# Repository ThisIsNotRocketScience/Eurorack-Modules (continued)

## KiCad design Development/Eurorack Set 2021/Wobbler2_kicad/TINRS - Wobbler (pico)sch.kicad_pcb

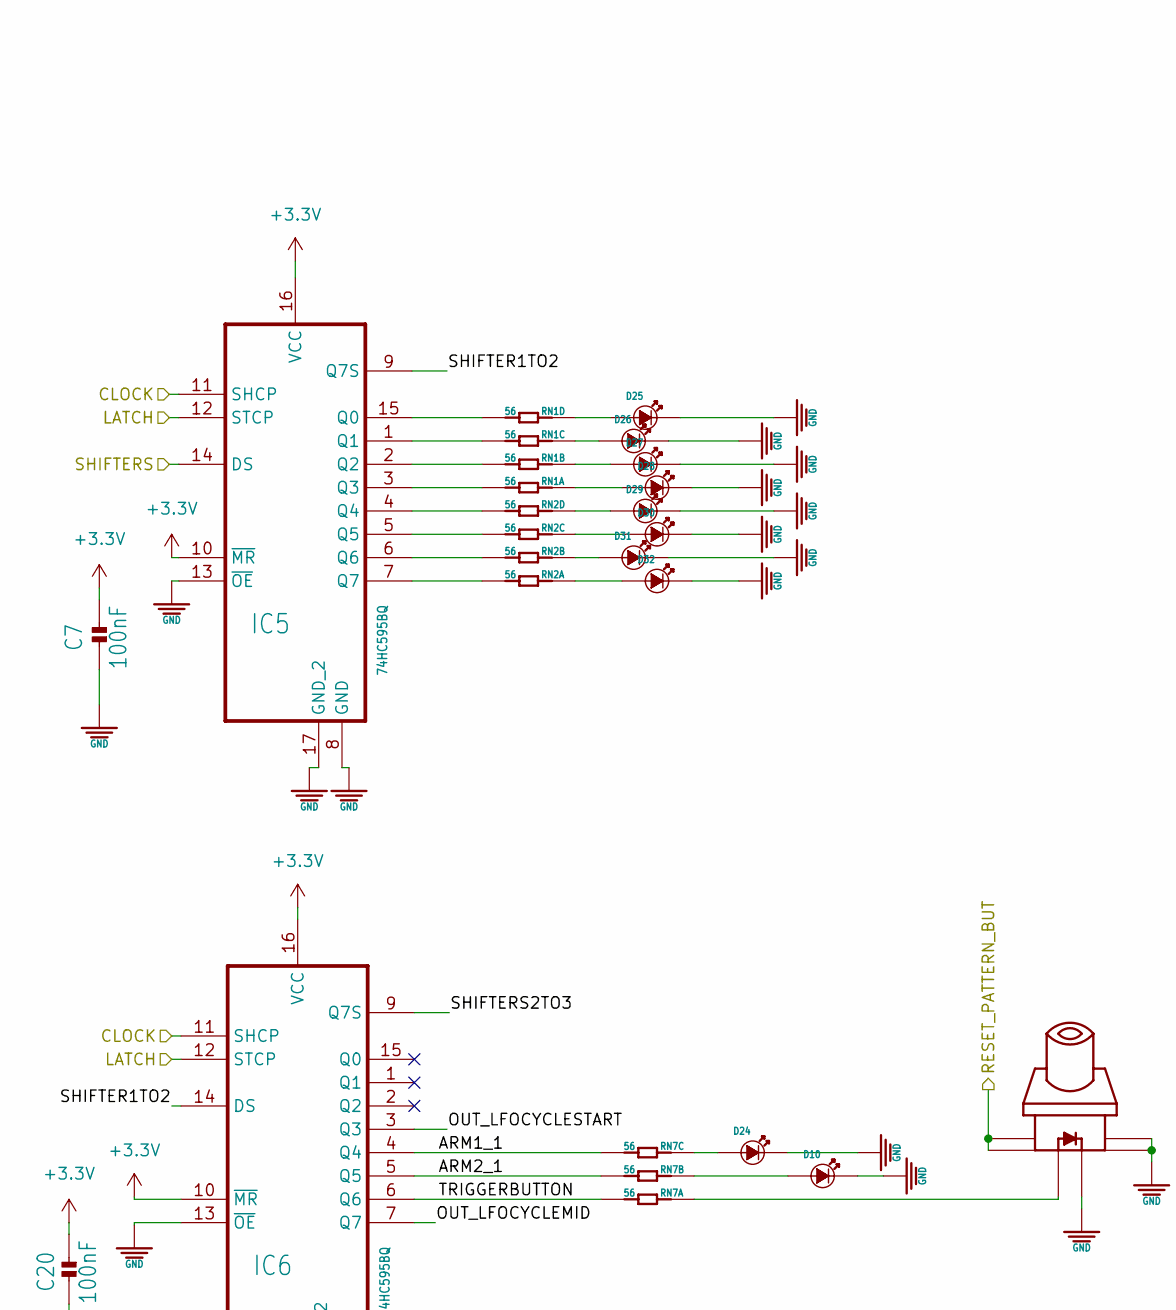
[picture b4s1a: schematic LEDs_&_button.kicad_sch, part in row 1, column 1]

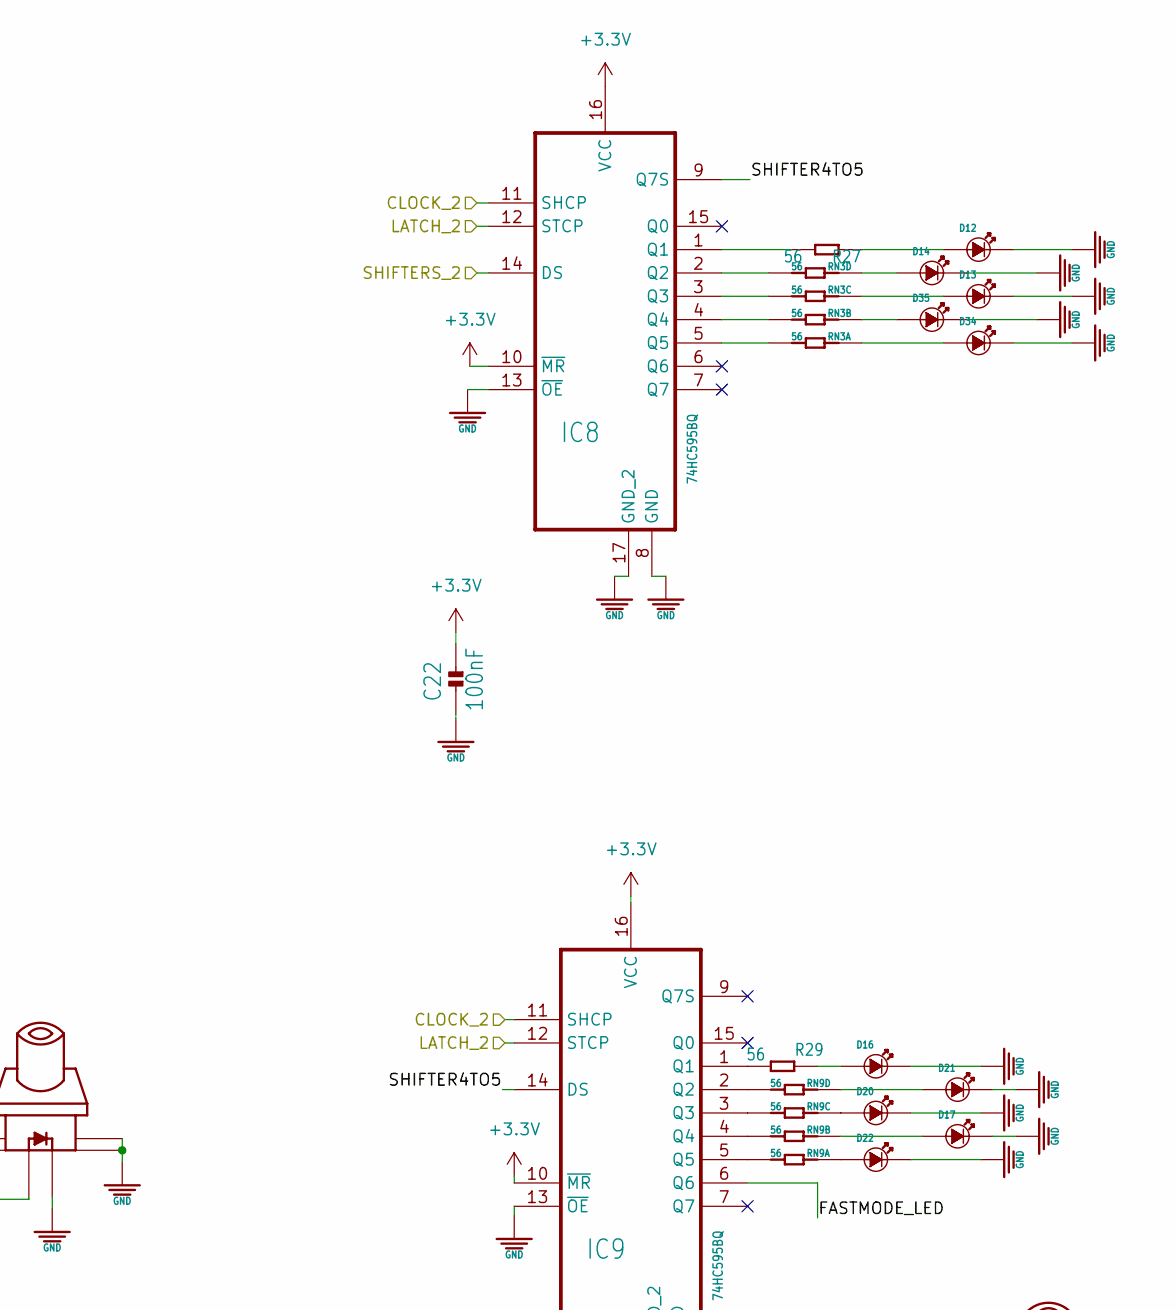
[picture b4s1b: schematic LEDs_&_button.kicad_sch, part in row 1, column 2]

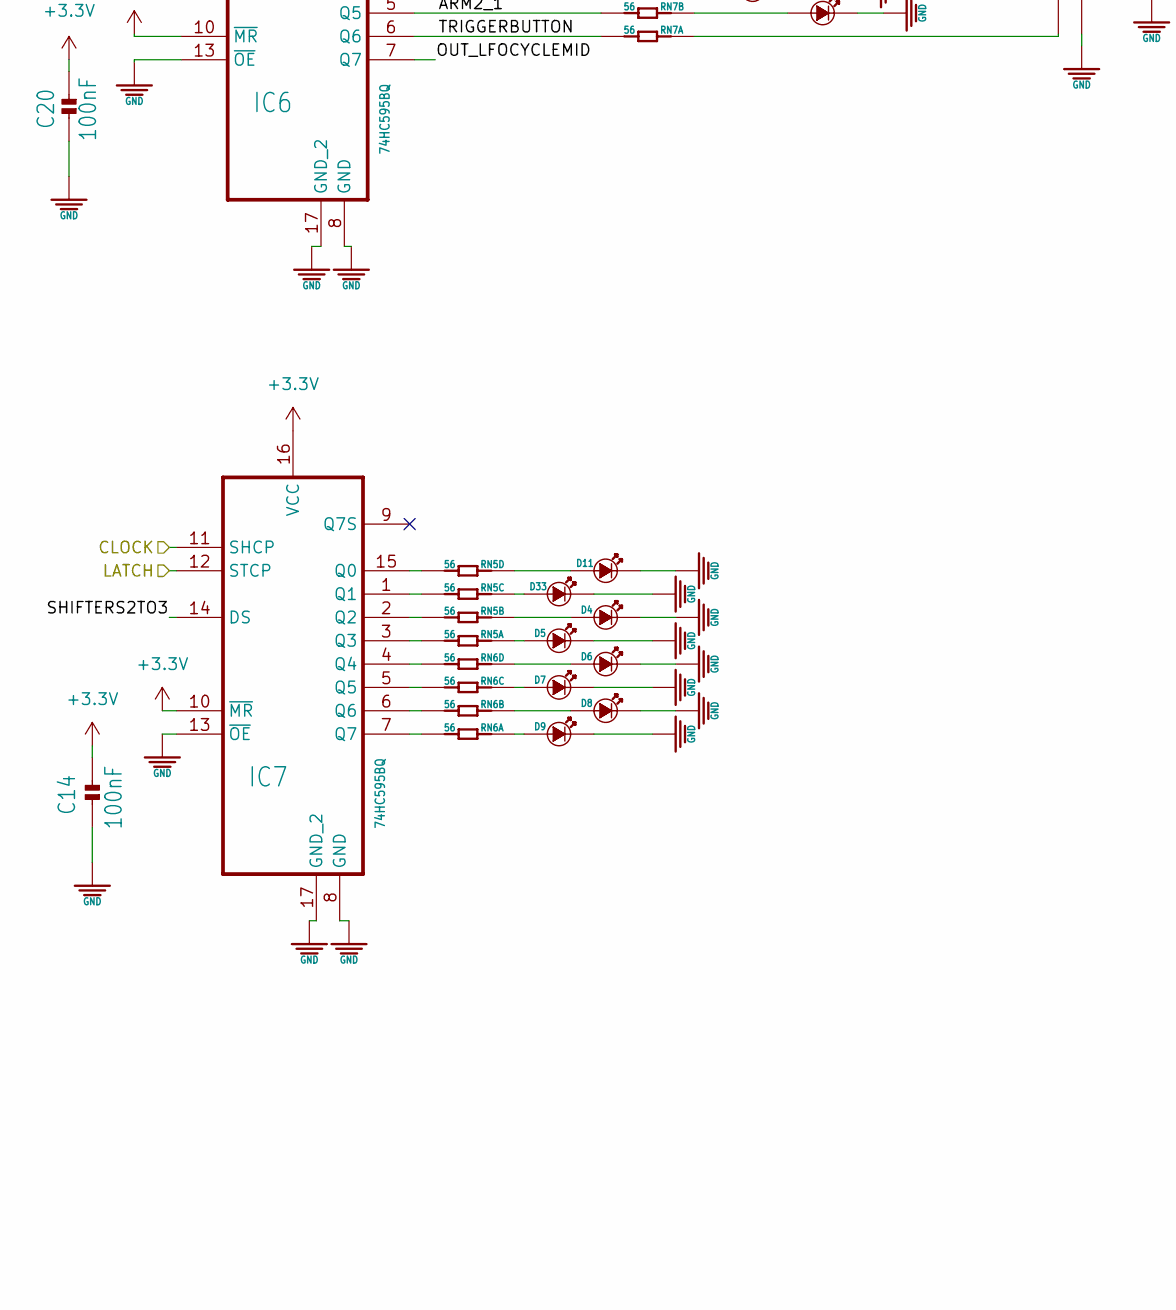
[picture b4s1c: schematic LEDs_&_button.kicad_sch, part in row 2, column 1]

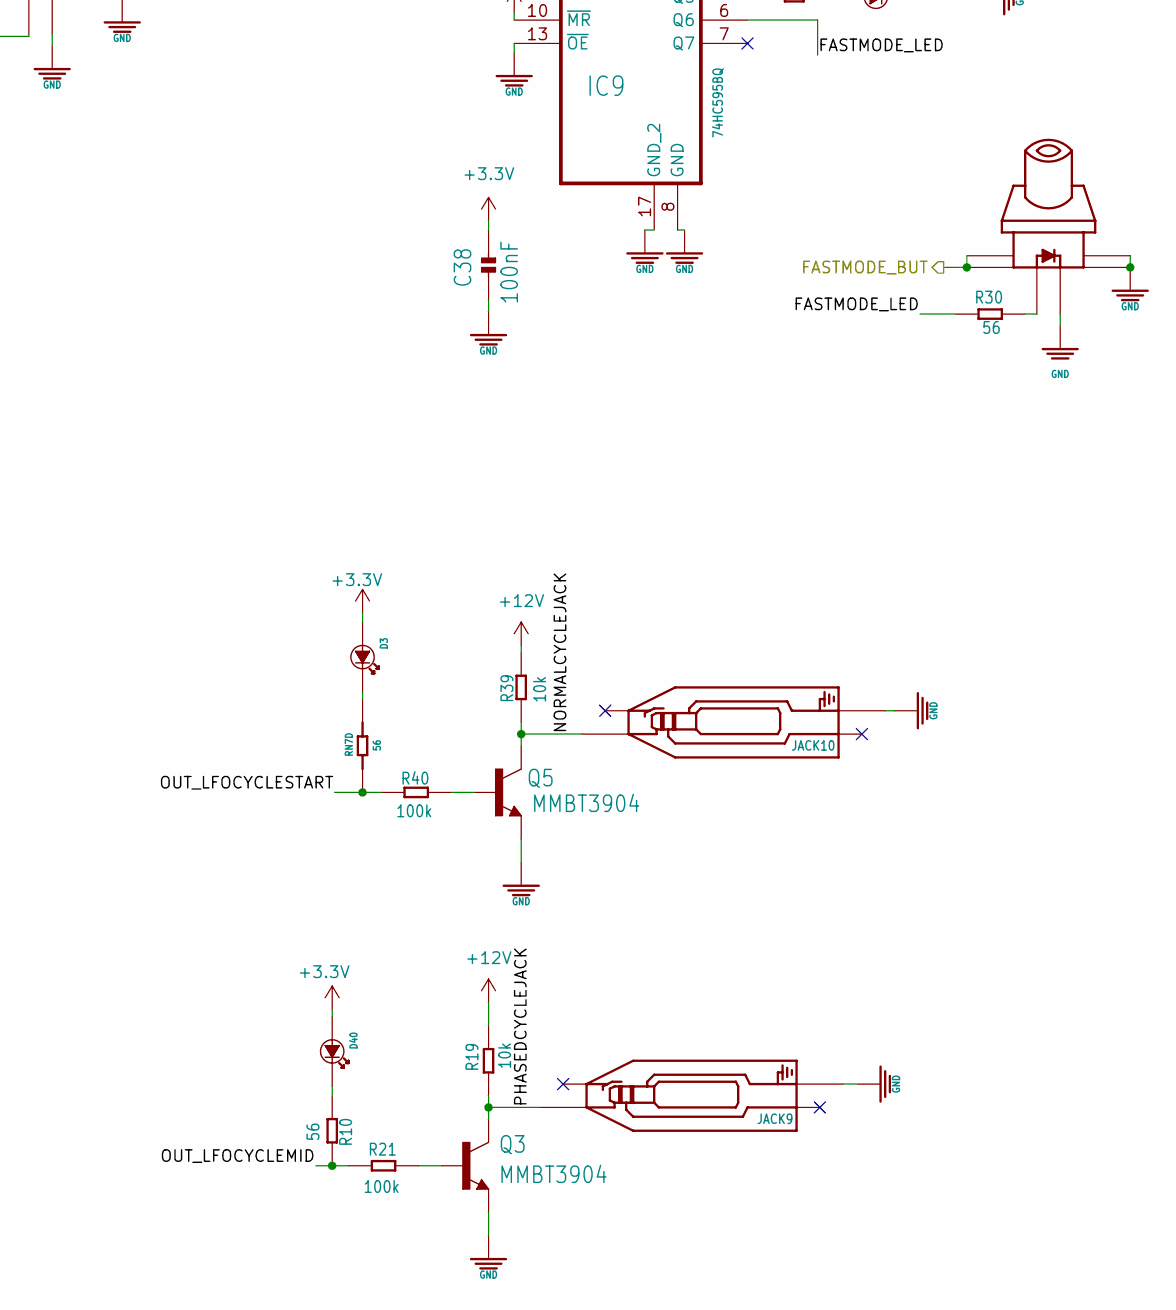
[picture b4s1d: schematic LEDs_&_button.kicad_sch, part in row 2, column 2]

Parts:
C7, C14, C20, C22, C38: 1759017; C0402
D3, D4, D5, D6, D7, D8, D9, D10, D11, D12, D13, D14, D16, D17, D20, D21, D22, D24, D25, D26, D27, D28, D29, D30, D31, D32, D33, D34, D35, D40: LED3MM; 3MMLED
IC5, IC6, IC7, IC8, IC9: NXP; QFN50P250X350X100-17N
JACK9, JACK10: AUDIO-JACK_SMALLSYMBOL; 3.5MM-JACK-SWITCH-13MM-NOHOLES-TESTPAD
Q3, Q5: 2336795; SOT23-BEC
R10, R19, R21, R27, R29, R30, R39, R40: unknown; R0603
RN1, RN2, RN3, RN5, RN6, RN7, RN9: 56; 4X0402ARV341
U$1, U$28: SWITCH_W_LED_PB6149L-X-102YELLOW; PB6149L

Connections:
+12V: R19.2, R39.2; also elsewhere on the board
/LEDs & button/ARM1_1: IC6.4 (Q4), RN7.3 (1)
/LEDs & button/ARM2_1: IC6.5 (Q5), RN7.2 (1)
/LEDs & button/CLOCK: IC5.11 (SHCP), IC6.11 (SHCP), IC7.11 (SHCP); also elsewhere on the board
/LEDs & button/CLOCK_2: IC8.11 (SHCP), IC9.11 (SHCP); also elsewhere on the board
/LEDs & button/FASTMODE_BUT: U$28.1, U$28.2; also elsewhere on the board
/LEDs & button/FASTMODE_LED: IC9.6 (Q6), R30.2
/LEDs & button/LATCH: IC5.12 (STCP), IC6.12 (STCP), IC7.12 (STCP); also elsewhere on the board
/LEDs & button/LATCH_2: IC8.12 (STCP), IC9.12 (STCP); also elsewhere on the board
/LEDs & button/NORMALCYCLEJACK: JACK10.TIP, Q5.C, R39.1
/LEDs & button/OUT_LFOCYCLEMID: IC6.7 (Q7), R10.2, R21.1
/LEDs & button/OUT_LFOCYCLESTART: IC6.3 (Q3), R40.1, RN7.4 (1)
/LEDs & button/PHASEDCYCLEJACK: JACK9.TIP, Q3.C, R19.1
/LEDs & button/RESET_PATTERN_BUT: U$1.1, U$1.2; also elsewhere on the board
/LEDs & button/SHIFTER1TO2: IC5.9 (Q7S), IC6.14 (DS)
/LEDs & button/SHIFTER4TO5: IC8.9 (Q7S), IC9.14 (DS)
/LEDs & button/SHIFTERS: IC5.14 (DS); also elsewhere on the board
/LEDs & button/SHIFTERS2TO3: IC6.9 (Q7S), IC7.14 (DS)
/LEDs & button/SHIFTERS_2: IC8.14 (DS); also elsewhere on the board
/LEDs & button/TRIGGERBUTTON: IC6.6 (Q6), RN7.1
GND: C7.1, C14.1, C20.1, C22.1, C38.1, D4.-, D5.-, D6.-, D7.-, D8.-, D9.-, D10.-, D11.-, D12.-, D13.-, D14.-, D16.-, D17.-, D20.-, D21.-, D22.-, D24.-, D25.-, D26.-, D27.-, D28.-, D29.-, D30.-, D31.-, D32.-, D33.-, D34.-, D35.-, IC5.8 (GND), IC5.13 (~OE), IC5.17 (GND_2), IC6.8 (GND), IC6.13 (~OE), IC6.17 (GND_2), IC7.8 (GND), IC7.13 (~OE), IC7.17 (GND_2), IC8.8 (GND), IC8.13 (~OE), IC8.17 (GND_2), IC9.8 (GND), IC9.13 (~OE), IC9.17 (GND_2), JACK9.RING, JACK10.RING, Q3.E, Q5.E, U$1.3, U$1.4, U$1.LEDNEG (NEG), U$28.3, U$28.4, U$28.LEDNEG (NEG); also elsewhere on the board
unnamed: D3.-, RN7.5 (2)
unnamed: D4.+, RN5.7 (2)
unnamed: D5.+, RN5.8 (2)
unnamed: D6.+, RN6.5 (2)
unnamed: D7.+, RN6.6 (2)
unnamed: D8.+, RN6.7 (2)
unnamed: D9.+, RN6.8 (2)
unnamed: D10.+, RN7.7 (2)
unnamed: D11.+, RN5.5 (2)
unnamed: D12.+, R27.1
unnamed: D13.+, RN3.6 (2)
unnamed: D14.+, RN3.5 (2)
unnamed: D16.+, R29.1
unnamed: D17.+, RN9.7 (2)
unnamed: D20.+, RN9.6 (2)
unnamed: D21.+, RN9.5 (2)
unnamed: D22.+, RN9.8 (2)
unnamed: D24.+, RN7.6 (2)
unnamed: D25.+, RN1.5 (2)
unnamed: D26.+, RN1.6 (2)
unnamed: D27.+, RN1.7 (2)
unnamed: D28.+, RN1.8 (2)
unnamed: D29.+, RN2.5 (2)
unnamed: D30.+, RN2.6 (2)
unnamed: D31.+, RN2.7 (2)
unnamed: D32.+, RN2.8 (2)
unnamed: D33.+, RN5.6 (2)
unnamed: D34.+, RN3.8 (2)
unnamed: D35.+, RN3.7 (2)
unnamed: D40.-, R10.1
unnamed: IC5.1 (Q1), RN1.3 (1)
unnamed: IC5.2 (Q2), RN1.2 (1)
unnamed: IC5.3 (Q3), RN1.1
unnamed: IC5.4 (Q4), RN2.4 (1)
unnamed: IC5.5 (Q5), RN2.3 (1)
unnamed: IC5.6 (Q6), RN2.2 (1)
unnamed: IC5.7 (Q7), RN2.1
unnamed: IC5.15 (Q0), RN1.4 (1)
unnamed: IC7.1 (Q1), RN5.3 (1)
unnamed: IC7.2 (Q2), RN5.2 (1)
unnamed: IC7.3 (Q3), RN5.1
unnamed: IC7.4 (Q4), RN6.4 (1)
unnamed: IC7.5 (Q5), RN6.3 (1)
unnamed: IC7.6 (Q6), RN6.2 (1)
unnamed: IC7.7 (Q7), RN6.1
unnamed: IC7.15 (Q0), RN5.4 (1)
unnamed: IC8.1 (Q1), R27.2
unnamed: IC8.2 (Q2), RN3.4 (1)
unnamed: IC8.3 (Q3), RN3.3 (1)
unnamed: IC8.4 (Q4), RN3.2 (1)
unnamed: IC8.5 (Q5), RN3.1
unnamed: IC9.1 (Q1), R29.2
unnamed: IC9.2 (Q2), RN9.4 (1)
unnamed: IC9.3 (Q3), RN9.3 (1)
unnamed: IC9.4 (Q4), RN9.2 (1)
unnamed: IC9.5 (Q5), RN9.1
unnamed: Q3.B, R21.2
unnamed: Q5.B, R40.2
unnamed: R30.1, U$28.LEDPOS (POS)
unnamed: RN7.8 (2), U$1.LEDPOS (POS)

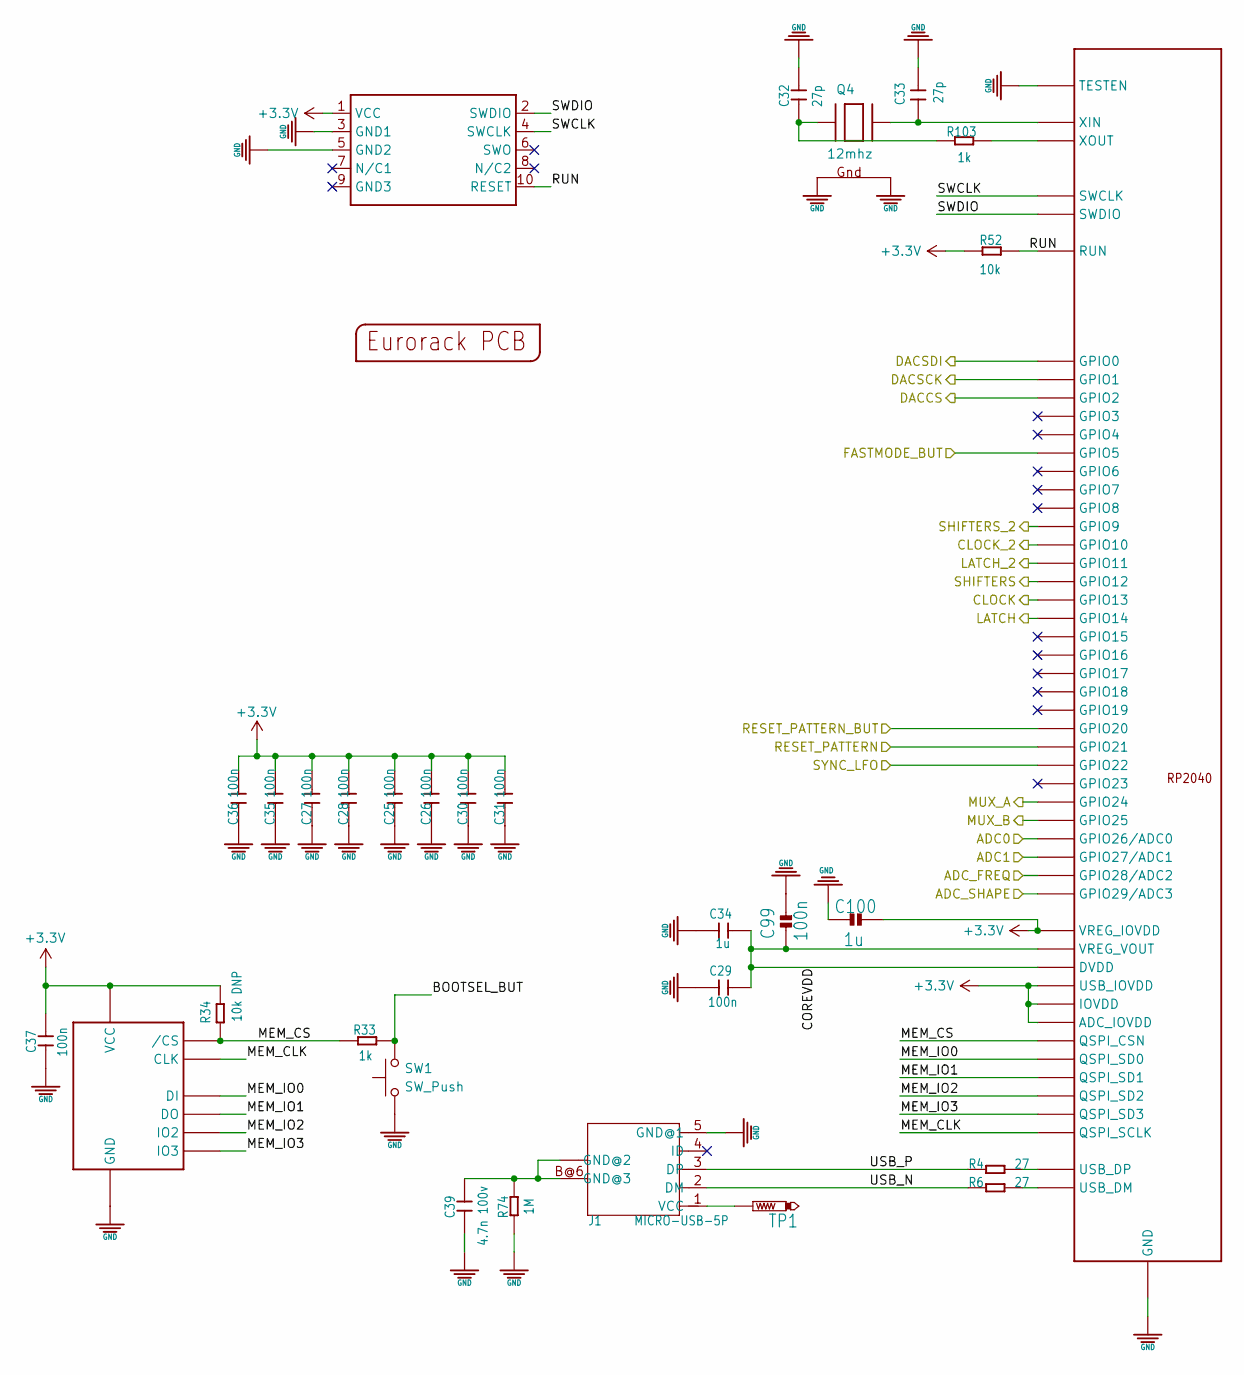
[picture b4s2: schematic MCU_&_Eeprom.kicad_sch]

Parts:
C25, C26, C27, C28, C29, C30, C31, C35, C36, C37, C99: 100n; C0402
C32, C33: 27p; C0402
C34, C100: 1u; C0402
C39: 4.7n 100v; C3216
J1: MICRO-USB-5P; C132563
OUTLINE1: unknown; EURORACK12HPPCB
Q4: 12mhz; NX3225
R4, R6: 27; R0402
R33, R103: 1k; R0402
R34: 10k DNP; R0402
R52: 10k; R0402
R74: 1M; R0603
SW1: SW_Push
SWD2: unknown; M50-3600542
TP1: PTR1B1,27; B1,27
U$2: RP2040; QFN-56
U$25: W25Q256JVEIQTR; SOIC-8

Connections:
/DAC/DACCS: U$2.P$4 (GPIO2); also elsewhere on the board
/DAC/DACSCK: U$2.P$3 (GPIO1); also elsewhere on the board
/DAC/DACSDI: U$2.P$2 (GPIO0); also elsewhere on the board
/Inputs & Knobs/ADC0: U$2.P$38 (GPIO26/ADC0); also elsewhere on the board
/Inputs & Knobs/ADC1: U$2.P$39 (GPIO27/ADC1); also elsewhere on the board
/Inputs & Knobs/ADC_FREQ: U$2.P$40 (GPIO28/ADC2); also elsewhere on the board
/Inputs & Knobs/ADC_SHAPE: U$2.P$41 (GPIO29/ADC3); also elsewhere on the board
/Inputs & Knobs/MUX_A: U$2.P$36 (GPIO24); also elsewhere on the board
/Inputs & Knobs/MUX_B: U$2.P$37 (GPIO25); also elsewhere on the board
/Inputs & Knobs/RESET_PATTERN: U$2.P$32 (GPIO21); also elsewhere on the board
/Inputs & Knobs/SYNC_LFO: U$2.P$34 (GPIO22); also elsewhere on the board
/LEDs & button/CLOCK: U$2.P$16 (GPIO13); also elsewhere on the board
/LEDs & button/CLOCK_2: U$2.P$13 (GPIO10); also elsewhere on the board
/LEDs & button/FASTMODE_BUT: U$2.P$5 (GPIO3); also elsewhere on the board
/LEDs & button/LATCH: U$2.P$17 (GPIO14); also elsewhere on the board
/LEDs & button/LATCH_2: U$2.P$14 (GPIO11); also elsewhere on the board
/LEDs & button/RESET_PATTERN_BUT: U$2.P$31 (GPIO20); also elsewhere on the board
/LEDs & button/SHIFTERS: U$2.P$15 (GPIO12); also elsewhere on the board
/LEDs & button/SHIFTERS_2: U$2.P$12 (GPIO9); also elsewhere on the board
/MCU & Eeprom/BOOTSEL_BUT: R33.2, SW1.2
/MCU & Eeprom/COREVDD: C29.1, C34.1, C99.1, U$2.P$23 (DVDD), U$2.P$45 (VREG_VOUT), U$2.P$50 (DVDD)
/MCU & Eeprom/EEPROM_SCL: U$2.P$7 (GPIO5); also elsewhere on the board
/MCU & Eeprom/EEPROM_SDA: U$2.P$6 (GPIO4); also elsewhere on the board
/MCU & Eeprom/MEM_CLK: U$2.P$52 (QSPI_SCLK), U$25.6 (CLK)
/MCU & Eeprom/MEM_CS: R33.1, R34.1, U$2.P$56 (QSPI_CSN), U$25.1 (/CS)
/MCU & Eeprom/MEM_IO0: U$2.P$53 (QSPI_SD0), U$25.5 (DI)
/MCU & Eeprom/MEM_IO1: U$2.P$55 (QSPI_SD1), U$25.2 (DO)
/MCU & Eeprom/MEM_IO2: U$2.P$54 (QSPI_SD2), U$25.3 (IO2)
/MCU & Eeprom/MEM_IO3: U$2.P$51 (QSPI_SD3), U$25.7 (IO3)
/MCU & Eeprom/RUN: R52.2, SWD2.10 (RESET), U$2.P$26 (RUN)
/MCU & Eeprom/SWCLK: SWD2.4 (SWCLK), U$2.P$24 (SWCLK)
/MCU & Eeprom/SWDIO: SWD2.2 (SWDIO), U$2.P$25 (SWDIO)
/MCU & Eeprom/USB_N: J1.2 (DM), R6.1
/MCU & Eeprom/USB_P: J1.3 (DP), R4.1
GND: C25.1, C26.1, C27.1, C28.1, C29.2, C30.1, C31.1, C32.2, C33.2, C34.2, C35.1, C36.1, C37.1, C39.1, C99.2, C100.2, J1.5 (GND@1), Q4.2 (G2), Q4.4 (G1), R74.1, SW1.1, SWD2.3 (GND1), SWD2.5 (GND2), U$2.GND, U$2.P$19 (TESTEN), U$25.4 (GND); also elsewhere on the board
unnamed: C32.1, Q4.1 (X1), R103.1
unnamed: C33.1, Q4.3 (X2), U$2.P$20 (XIN)
unnamed: C39.2, J1.B@1 (GND@2), J1.B@2 (GND@2), J1.B@3 (GND@2), J1.B@4 (GND@2), J1.B@5 (GND@2), J1.B@6 (GND@3), J1.B@7 (GND@2), J1.B@8 (GND@2), J1.B@9 (GND@2), J1.B@10 (GND@2), J1.B@11 (GND@2), J1.B@12 (GND@2), R74.2
unnamed: J1.1 (VCC), TP1.TP
unnamed: R4.2, U$2.P$47 (USB_DP)
unnamed: R6.2, U$2.P$46 (USB_DM)
unnamed: R103.2, U$2.P$21 (XOUT)

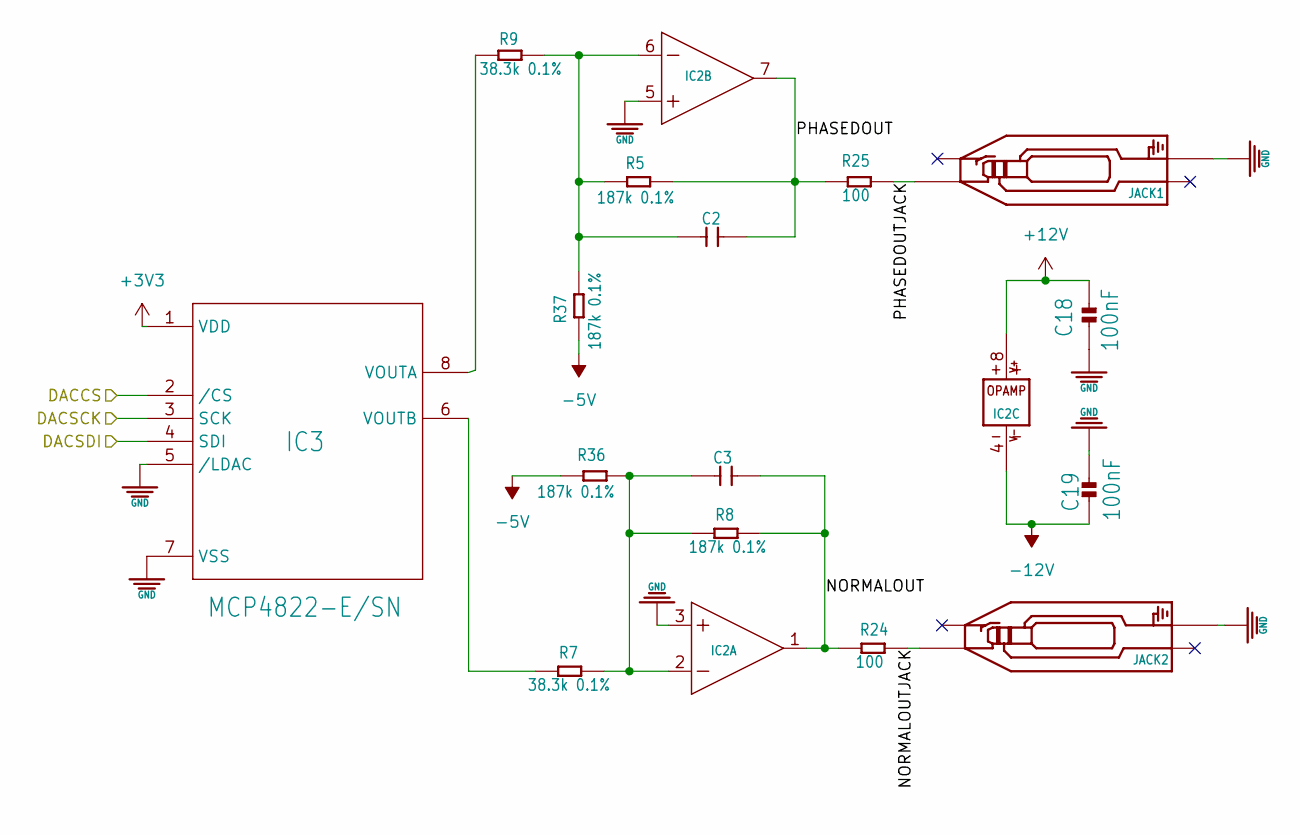
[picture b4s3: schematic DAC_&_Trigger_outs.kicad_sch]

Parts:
C2: unknown; C0603
C3: unknown
C18, C19: 1759017; C0402
IC2: TL072; SO08
IC3: MICROCHIP; SOIC8-N_MC
JACK1, JACK2: AUDIO-JACK_SMALLSYMBOL; 3.5MM-JACK-SWITCH-13MM-NOHOLES-TESTPAD
R5, R7, R8, R9, R24, R25, R36, R37: unknown; R0603

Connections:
+12V: C18.2, IC2.8 (V+); also elsewhere on the board
-5V: R36.2, R37.2; also elsewhere on the board
-12V: C19.2, IC2.4 (V-); also elsewhere on the board
/DAC/DACCS: IC3.2 (/CS); also elsewhere on the board
/DAC/DACSCK: IC3.3 (SCK); also elsewhere on the board
/DAC/DACSDI: IC3.4 (SDI); also elsewhere on the board
/DAC/NORMALOUT: C3.2, IC2.1 (OUT), R8.1, R24.2
/DAC/NORMALOUTJACK: JACK2.TIP, R24.1
/DAC/PHASEDOUT: C2.2, IC2.7 (OUT), R5.1, R25.2
/DAC/PHASEDOUTJACK: JACK1.TIP, R25.1
GND: C18.1, C19.1, IC2.3 (+IN), IC2.5 (+IN), IC3.5 (/LDAC), IC3.7 (VSS), JACK1.RING, JACK2.RING; also elsewhere on the board
unnamed: C2.1, IC2.6 (-IN), R5.2, R9.1, R37.1
unnamed: C3.1, IC2.2 (-IN), R7.1, R8.2, R36.1
unnamed: IC3.6 (VOUTB), R7.2
unnamed: IC3.8 (VOUTA), R9.2

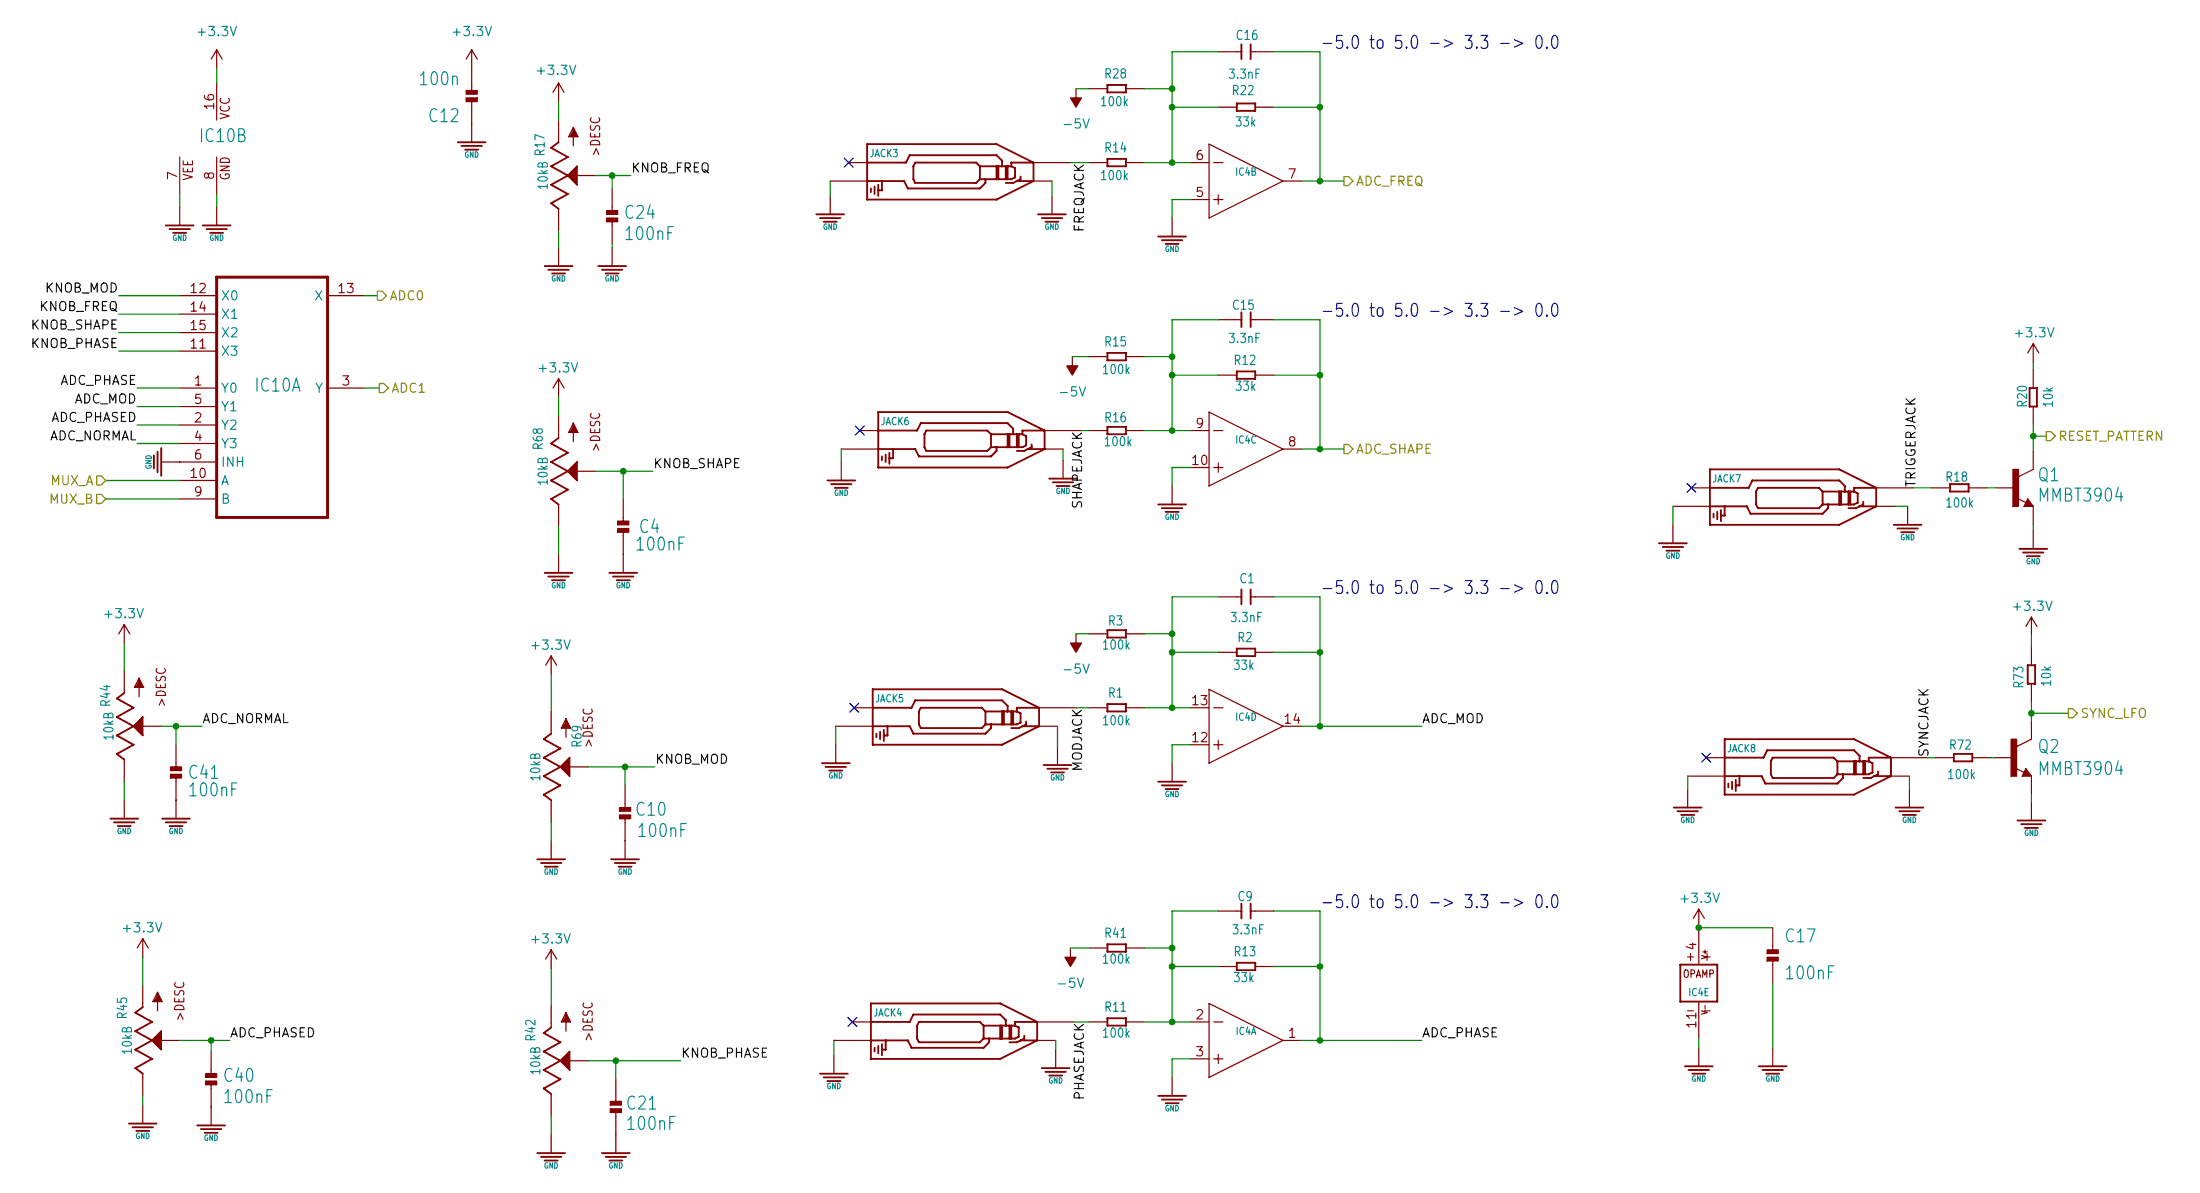
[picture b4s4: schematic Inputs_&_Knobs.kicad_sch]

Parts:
C1, C9, C15, C16: unknown; C0603
C4, C10, C17, C21, C24, C40, C41: 1759017; C0402
C12: 100n; C0402
IC4: 1605572; SO14
IC10: 4052D; SO16
JACK3, JACK4, JACK5, JACK6, JACK7, JACK8: AUDIO-JACK_SMALLSYMBOL; 3.5MM-JACK-SWITCH-13MM-NOHOLES-TESTPAD
Q1, Q2: 2336795; SOT23-BEC
R1, R2, R3, R11, R12, R13, R14, R15, R16, R18, R20, R22, R28, R41, R72, R73: unknown; R0603
R17, R42, R44, R45, R68, R69: unknown; ALPS_POT_SQUAREHOLES

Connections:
-5V: R3.2, R15.2, R28.2, R41.2; also elsewhere on the board
/Inputs & Knobs/ADC0: IC10.13 (X); also elsewhere on the board
/Inputs & Knobs/ADC1: IC10.3 (Y); also elsewhere on the board
/Inputs & Knobs/ADC_FREQ: C16.2, IC4.7 (OUT), R22.1; also elsewhere on the board
/Inputs & Knobs/ADC_MOD: C1.2, IC4.14 (OUT), IC10.5 (Y1), R2.1
/Inputs & Knobs/ADC_NORMAL: C41.1, IC10.4 (Y3), R44.P$2 (S)
/Inputs & Knobs/ADC_PHASE: C9.2, IC4.1 (OUT), IC10.1 (Y0), R13.1
/Inputs & Knobs/ADC_PHASED: C40.1, IC10.2 (Y2), R45.P$2 (S)
/Inputs & Knobs/ADC_SHAPE: C15.2, IC4.8 (OUT), R12.1; also elsewhere on the board
/Inputs & Knobs/FREQJACK: JACK3.TIP, R14.2
/Inputs & Knobs/KNOB_FREQ: C24.1, IC10.14 (X1), R17.P$2 (S)
/Inputs & Knobs/KNOB_MOD: C10.1, IC10.12 (X0), R69.P$2 (S)
/Inputs & Knobs/KNOB_PHASE: C21.1, IC10.11 (X3), R42.P$2 (S)
/Inputs & Knobs/KNOB_SHAPE: C4.1, IC10.15 (X2), R68.P$2 (S)
/Inputs & Knobs/MODJACK: JACK5.TIP, R1.2
/Inputs & Knobs/MUX_A: IC10.10 (A); also elsewhere on the board
/Inputs & Knobs/MUX_B: IC10.9 (B); also elsewhere on the board
/Inputs & Knobs/PHASEJACK: JACK4.TIP, R11.2
/Inputs & Knobs/RESET_PATTERN: Q1.C, R20.1; also elsewhere on the board
/Inputs & Knobs/SHAPEJACK: JACK6.TIP, R16.2
/Inputs & Knobs/SYNCJACK: JACK8.TIP, R72.1
/Inputs & Knobs/SYNC_LFO: Q2.C, R73.1; also elsewhere on the board
/Inputs & Knobs/TRIGGERJACK: JACK7.TIP, R18.1
GND: C4.2, C10.2, C12.1, C17.2, C21.2, C24.2, C40.2, C41.2, IC4.3 (+IN), IC4.5 (+IN), IC4.10 (+IN), IC4.11 (V-), IC4.12 (+IN), IC10.6 (INH), IC10.7 (VEE), IC10.8 (GND), JACK3.RING, JACK3.SWITCH, JACK4.RING, JACK4.SWITCH, JACK5.RING, JACK5.SWITCH, JACK6.RING, JACK6.SWITCH, JACK7.RING, JACK7.SWITCH, JACK8.RING, JACK8.SWITCH, Q1.E, Q2.E, R17.P$1 (E), R42.P$1 (E), R44.P$1 (E), R45.P$1 (E), R68.P$1 (E), R69.P$1 (E); also elsewhere on the board
unnamed: C1.1, IC4.13 (-IN), R1.1, R2.2, R3.1
unnamed: C9.1, IC4.2 (-IN), R11.1, R13.2, R41.1
unnamed: C15.1, IC4.9 (-IN), R12.2, R15.1, R16.1
unnamed: C16.1, IC4.6 (-IN), R14.1, R22.2, R28.1
unnamed: Q1.B, R18.2
unnamed: Q2.B, R72.2

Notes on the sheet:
-5.0 to 5.0 -> 3.3 -> 0.0

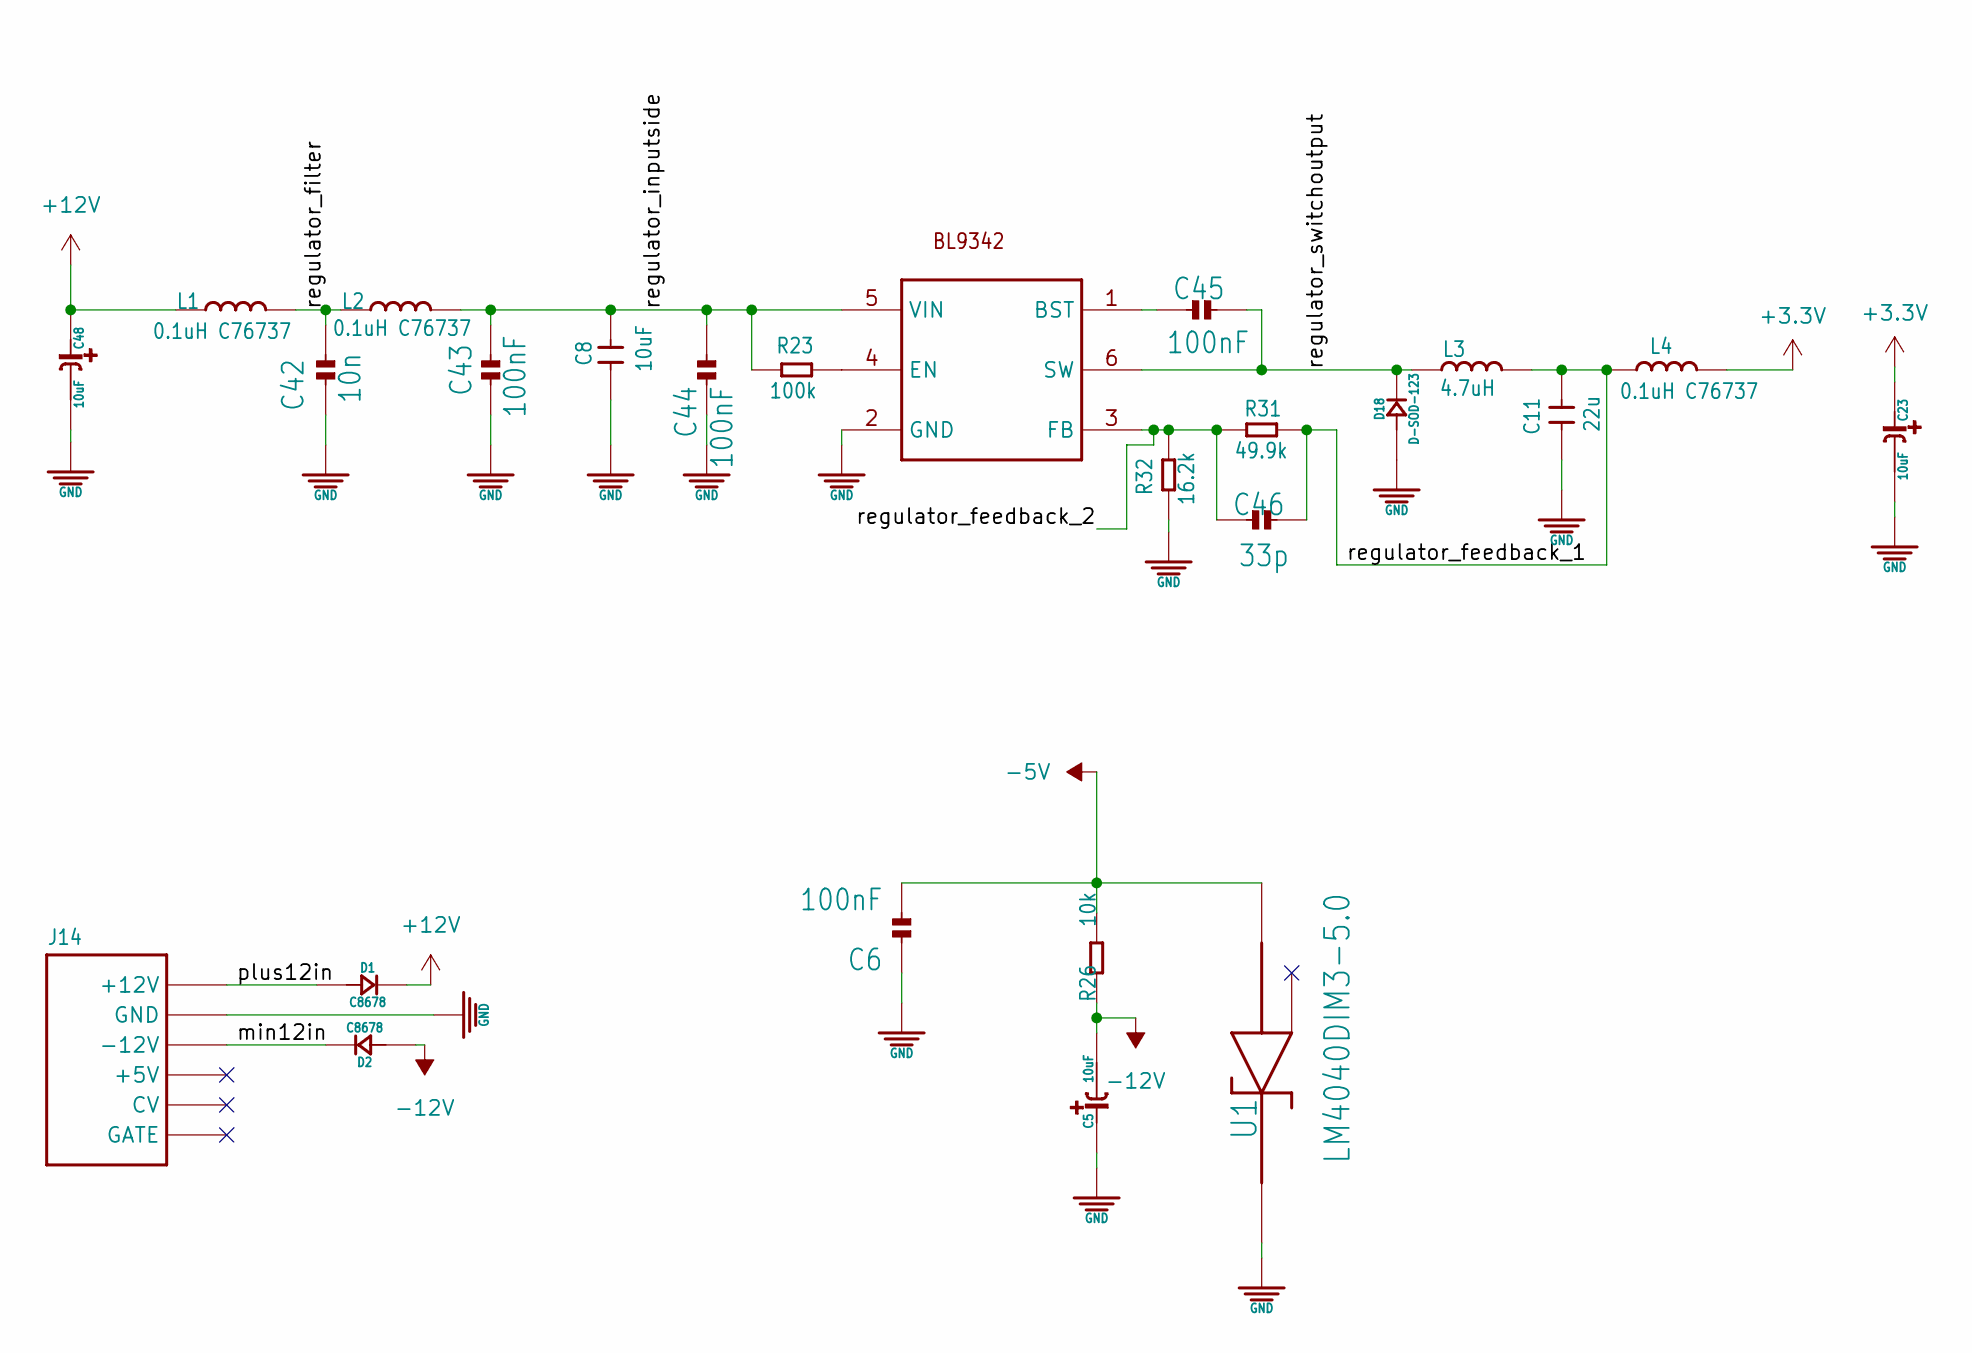
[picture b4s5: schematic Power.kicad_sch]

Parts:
C5, C23, C48: 197427; CASE-A_3216
C6: 1301804; C0402
C8: 10uF; C0805
C11: 22u; C0805
C42, C43, C44, C45, C46: 1759017; C0402
D1, D2: D-SMA; DO-214AC
D18: D-SOD-123; SOD123
J14: unknown; POWER_16_SHROUDED
L1, L2, L4: 0.1uH C76737; L0805
L3: 4.7uH; L0420
R23, R26, R31, R32: unknown; R0603
U1: 9778330; SOT95P237X112-3N
U$5: BL9342; SOT23-6

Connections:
+12V: C48.+ (1), D1.2 (-), L1.1; also elsewhere on the board
-5V: C6.2, R26.2, U1.2 (ANODE); also elsewhere on the board
-12V: C5.- (2), D2.1 (+), R26.1; also elsewhere on the board
/Power/min12in: D2.2 (-), J14.1 (-12V), J14.2 (-12V)
/Power/plus12in: D1.1 (+), J14.9 (+12V), J14.10 (+12V)
/Power/regulator_feedback_1: C11.2, C46.1, L3.2, L4.1, R31.1
/Power/regulator_feedback_2: C46.2, R31.2, R32.1, U$5.3 (FB)
/Power/regulator_filter: C42.2, L1.2, L2.1
/Power/regulator_inputside: C8.2, C43.2, C44.2, L2.2, R23.2, U$5.5 (VIN)
/Power/regulator_switchoutput: C45.1, D18.-, L3.1, U$5.6 (SW)
GND: C5.+ (1), C6.1, C8.1, C11.1, C23.- (2), C42.1, C43.1, C44.1, C48.- (2), D18.+, J14.3 (GND), J14.4 (GND), J14.5 (GND), J14.6 (GND), J14.7 (GND), J14.8 (GND), R32.2, U1.1 (CATHODE), U$5.2 (GND); also elsewhere on the board
unnamed: C45.2, U$5.1 (BST)
unnamed: J14.11 (+5V), J14.12 (+5V)
unnamed: J14.13 (CV), J14.14 (CV)
unnamed: J14.15 (GATE), J14.16 (GATE)
unnamed: R23.1, U$5.4 (EN)

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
